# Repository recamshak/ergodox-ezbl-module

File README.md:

# ErgoDox EZBL

A drop-in board for the ErgoDox EZ keyboard, using a Nice!Nano V2 running [ZMK](https://zmk.dev), giving you Bluetooth connectivity without any modifications to the case.

## Features

- Drop-in replacement for the original ErgoDox EZ PCB, no modifications to the case needed
- Bluetooth wireless via Nice!Nano V2
- [ZMK Studio](https://zmk.studio) support for real-time keymap editing

## Usage

Add this module to your ZMK config's `west.yml`:

```yaml
manifest:
  remotes:
    - name: ergodox-ezbl
      url-base: https://github.com/recamshak/ergodox-ezbl-module
  projects:
    - name: zmk
      remote: ergodox-ezbl
      revision: main
      import: app/west.yml
  self:
    path: config
```

Then reference the `ergodox_ezbl_left` and `ergodox_ezbl_right` shields in your build configuration.

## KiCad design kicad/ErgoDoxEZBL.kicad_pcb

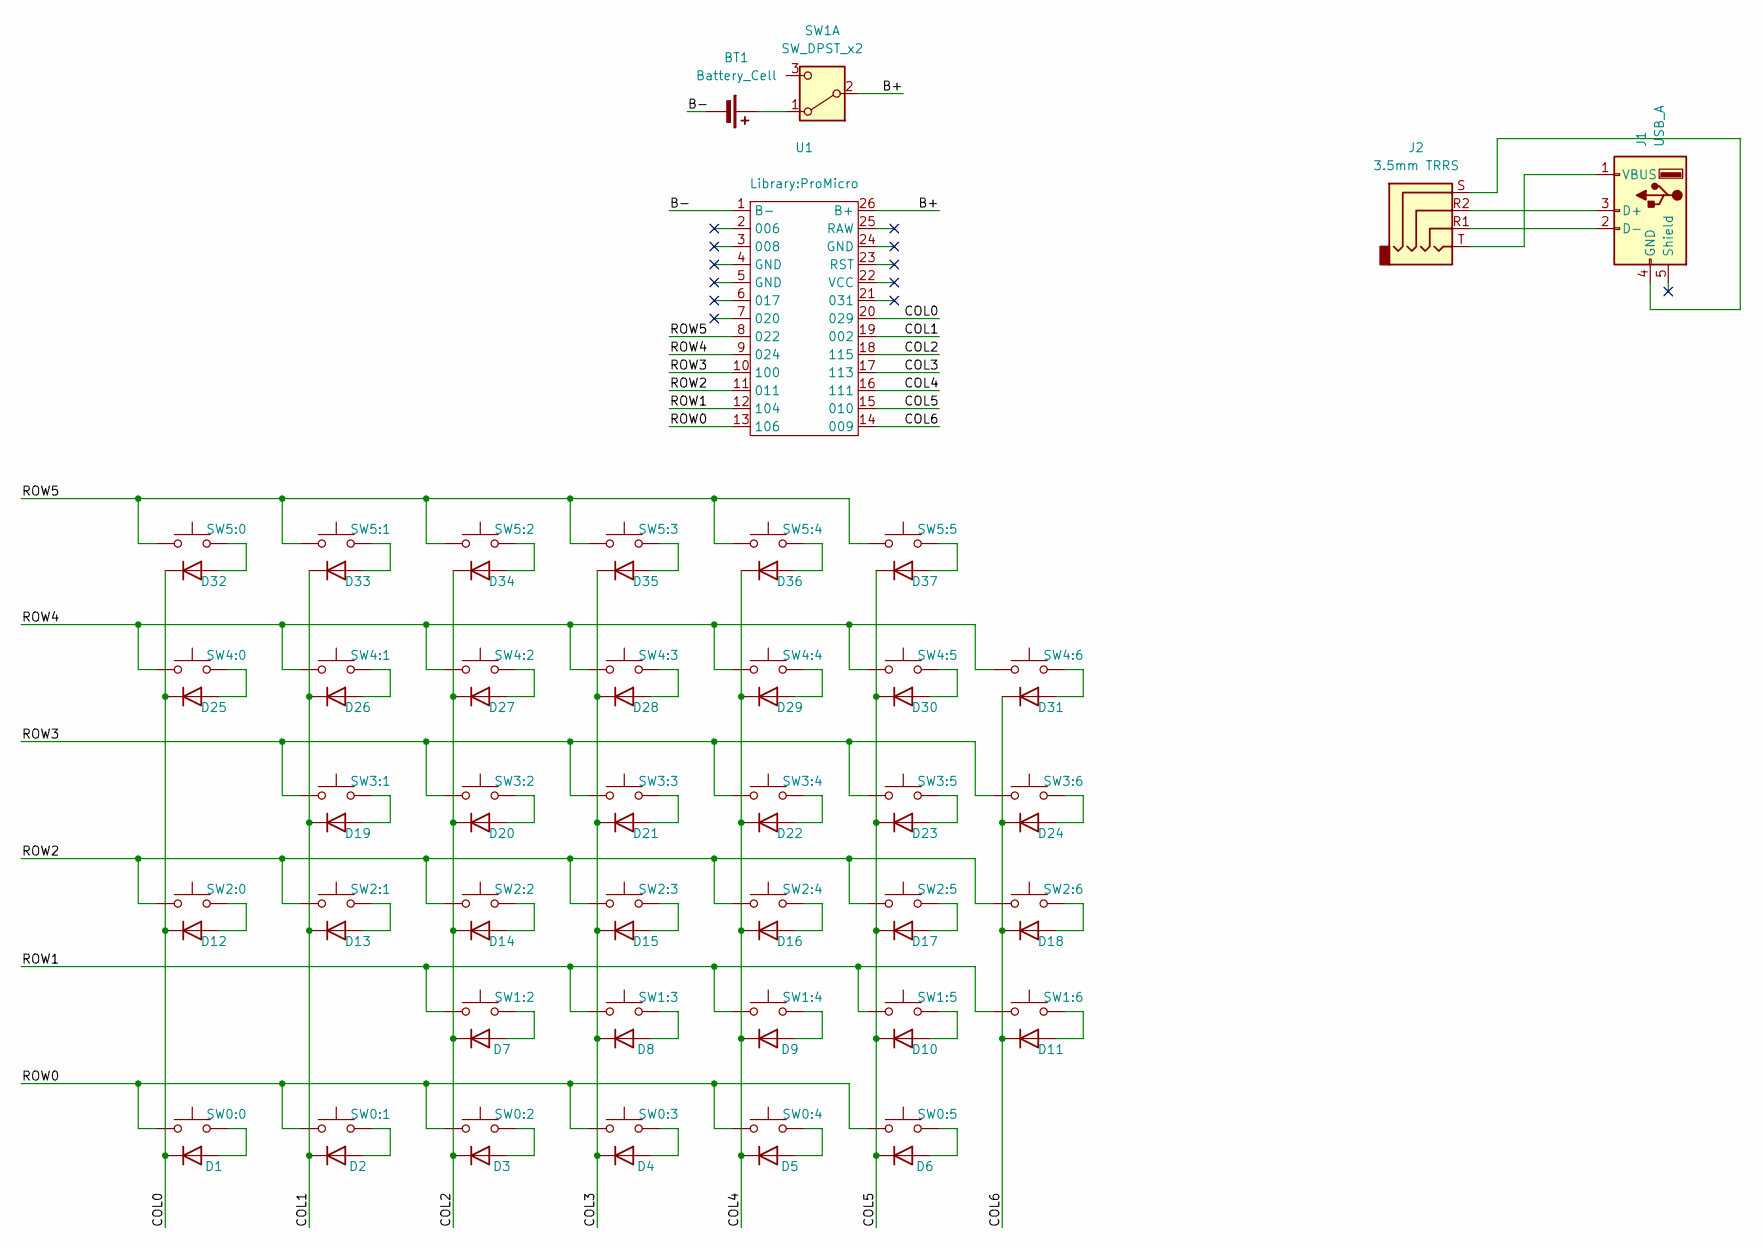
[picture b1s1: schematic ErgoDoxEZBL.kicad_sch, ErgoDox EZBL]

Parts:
BT1: Battery_Cell; SolderWire-0.1sqmm_1x02_P3.6mm_D0.4mm_OD1mm
D1, D2, D3, D4, D5, D6, D7, D8, D9, D10, D11, D12, D13, D14, D15, D16, D17, D18, D19, D20, D21, D22, D23, D24, D25, D26, D27, D28, D29, D30, D31, D32, D33, D34, D35, D36, D37: 1N4148; D_DO-35_SOD27_P7.62mm_Horizontal
J1: USB_A; SolderWire-0.1sqmm_1x04_P3.6mm_D0.4mm_OD1mm
J2: 3.5mm TRRS; SJ3-35094A
SW0:0, SW0:1, SW0:2, SW0:3, SW0:4, SW0:5, SW1:2, SW1:3, SW1:4, SW1:5, SW1:6, SW2:0, SW2:1, SW2:2, SW2:3, SW2:4, SW2:5, SW2:6, SW3:1, SW3:2, SW3:3, SW3:4, SW3:5, SW3:6, SW4:0, SW4:1, SW4:2, SW4:3, SW4:4, SW4:5, SW4:6, SW5:0, SW5:1, SW5:2, SW5:3, SW5:4, SW5:5: SW_Push; SW_Hotswap_Kailh_MX_1.00u
SW1: SW_DPST_x2; Power switch
U1: ProMicro

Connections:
/B+: SW1.2 (B), U1.26 (B+)
/B-: BT1.2 (-), U1.1 (B-)
/COL0: D1.1 (K), D12.1 (K), D25.1 (K), D32.1 (K), U1.20 (029)
/COL1: D2.1 (K), D13.1 (K), D19.1 (K), D26.1 (K), D33.1 (K), U1.19 (002)
/COL2: D3.1 (K), D7.1 (K), D14.1 (K), D20.1 (K), D27.1 (K), D34.1 (K), U1.18 (115)
/COL3: D4.1 (K), D8.1 (K), D15.1 (K), D21.1 (K), D28.1 (K), D35.1 (K), U1.17 (113)
/COL4: D5.1 (K), D9.1 (K), D16.1 (K), D22.1 (K), D29.1 (K), D36.1 (K), U1.16 (111)
/COL5: D6.1 (K), D10.1 (K), D17.1 (K), D23.1 (K), D30.1 (K), D37.1 (K), U1.15 (010)
/COL6: D11.1 (K), D18.1 (K), D24.1 (K), D31.1 (K), U1.14 (009)
/ROW0: SW0:0.1, SW0:1.1, SW0:2.1, SW0:3.1, SW0:4.1, SW0:5.1, U1.13 (106)
/ROW1: SW1:2.1, SW1:3.1, SW1:4.1, SW1:5.1, SW1:6.1, U1.12 (104)
/ROW2: SW2:0.1, SW2:1.1, SW2:2.1, SW2:3.1, SW2:4.1, SW2:5.1, SW2:6.1, U1.11
/ROW3: SW3:1.1, SW3:2.1, SW3:3.1, SW3:4.1, SW3:5.1, SW3:6.1, U1.10 (100)
/ROW4: SW4:0.1, SW4:1.1, SW4:2.1, SW4:3.1, SW4:4.1, SW4:5.1, SW4:6.1, U1.9 (024)
/ROW5: SW5:0.1, SW5:1.1, SW5:2.1, SW5:3.1, SW5:4.1, SW5:5.1, U1.8 (022)
unnamed: BT1.1 (+), SW1.1 (A)
unnamed: D1.2 (A), SW0:0.2
unnamed: D2.2 (A), SW0:1.2
unnamed: D3.2 (A), SW0:2.2
unnamed: D4.2 (A), SW0:3.2
unnamed: D5.2 (A), SW0:4.2
unnamed: D6.2 (A), SW0:5.2
unnamed: D7.2 (A), SW1:2.2
unnamed: D8.2 (A), SW1:3.2
unnamed: D9.2 (A), SW1:4.2
unnamed: D10.2 (A), SW1:5.2
unnamed: D11.2 (A), SW1:6.2
unnamed: D12.2 (A), SW2:0.2
unnamed: D13.2 (A), SW2:1.2
unnamed: D14.2 (A), SW2:2.2
unnamed: D15.2 (A), SW2:3.2
unnamed: D16.2 (A), SW2:4.2
unnamed: D17.2 (A), SW2:5.2
unnamed: D18.2 (A), SW2:6.2
unnamed: D19.2 (A), SW3:1.2
unnamed: D20.2 (A), SW3:2.2
unnamed: D21.2 (A), SW3:3.2
unnamed: D22.2 (A), SW3:4.2
unnamed: D23.2 (A), SW3:5.2
unnamed: D24.2 (A), SW3:6.2
unnamed: D25.2 (A), SW4:0.2
unnamed: D26.2 (A), SW4:1.2
unnamed: D27.2 (A), SW4:2.2
unnamed: D28.2 (A), SW4:3.2
unnamed: D29.2 (A), SW4:4.2
unnamed: D30.2 (A), SW4:5.2
unnamed: D31.2 (A), SW4:6.2
unnamed: D32.2 (A), SW5:0.2
unnamed: D33.2 (A), SW5:1.2
unnamed: D34.2 (A), SW5:2.2
unnamed: D35.2 (A), SW5:3.2
unnamed: D36.2 (A), SW5:4.2
unnamed: D37.2 (A), SW5:5.2
unnamed: J1.3 (D+), J2.R2
unnamed: J1.2 (D-), J2.R1
unnamed: J1.4 (GND), J2.S
unnamed: J1.1 (VBUS), J2.T

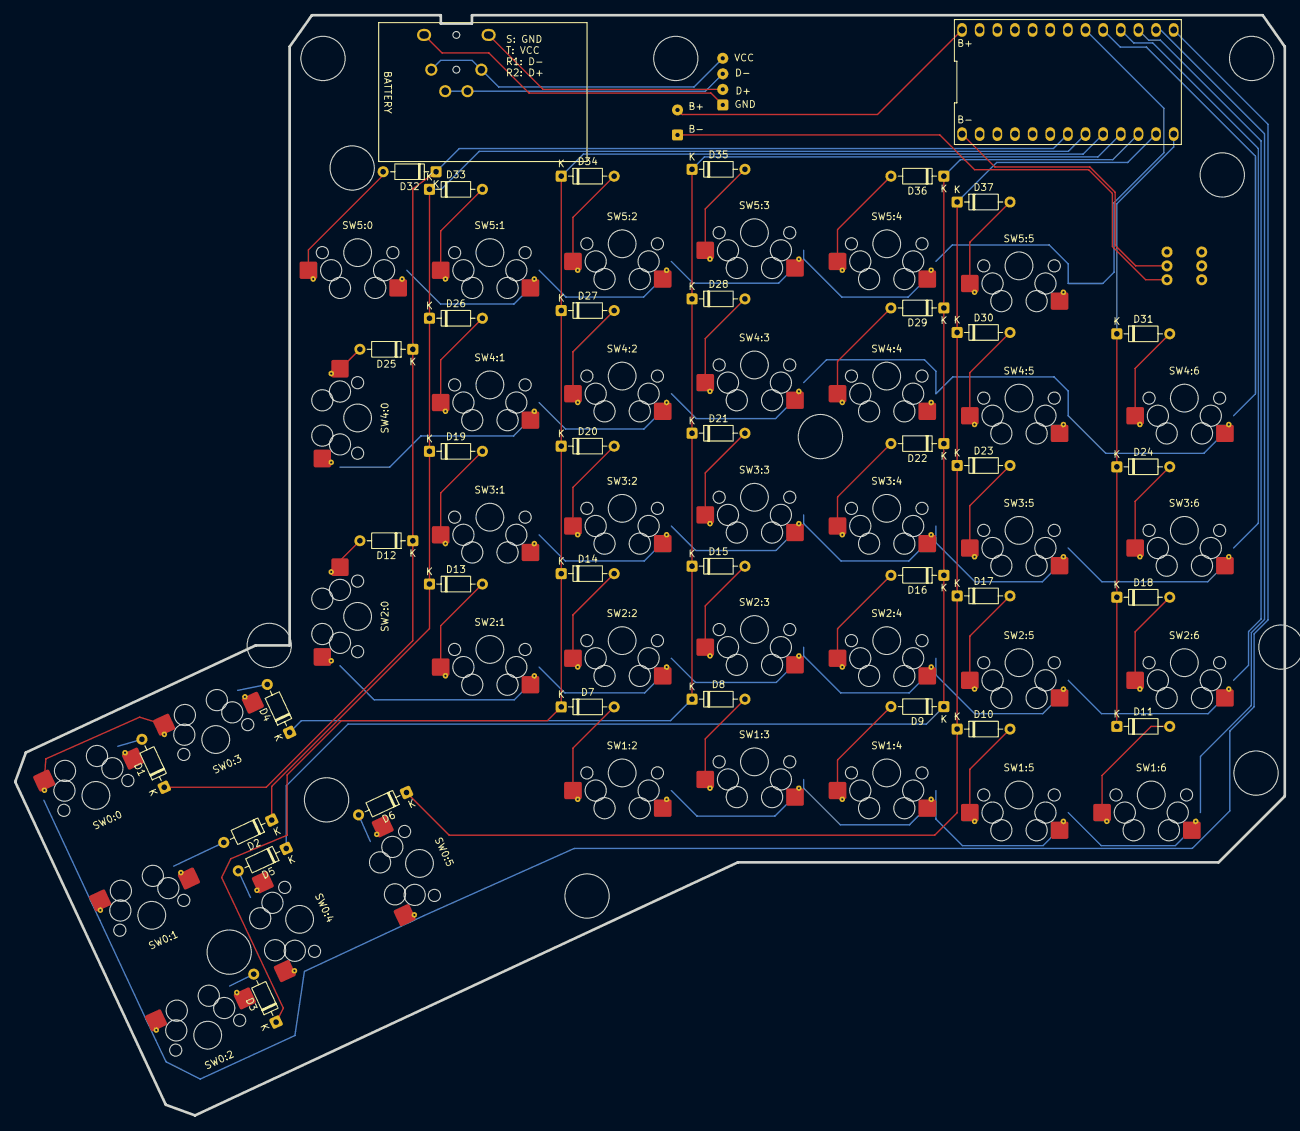
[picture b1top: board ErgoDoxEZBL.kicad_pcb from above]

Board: 2 copper layers, 182.8 x 158.4 mm, 79 parts (1 on the bottom side), 57 nets.

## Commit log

2026-03-02 Base Kconfig files
2026-03-03 Initial config
2026-03-03 Update build
2026-03-03 Fix dtsi file
2026-03-03 Fix imports
2026-03-03 Disable studio locking
2026-03-03 Add schematics & PCB
2026-03-03 Fix DC Jack footprint
2026-03-03 Fix MCU position
2026-03-05 NiceNano V2
2026-03-13 PCB v2
    - Fix DC jack footprint
    - Single reversible PCB for both split
2026-03-20 Build reset firmware
2026-03-20 Fix transform matrix and left split pinout.
2026-03-20 Fix left split pinout
2026-03-21 Fix left thumb columns mapping
2026-03-24 Enable peripheral battery level report
2026-04-03 USB connection via TRRS jack connector
